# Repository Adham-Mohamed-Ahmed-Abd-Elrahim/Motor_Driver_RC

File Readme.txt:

A PCB Chip for controlling RC car [LPC1768_Arduino Nano_MPU6050_RF L298N (motor driver)]
Software Used For designing: Eagle

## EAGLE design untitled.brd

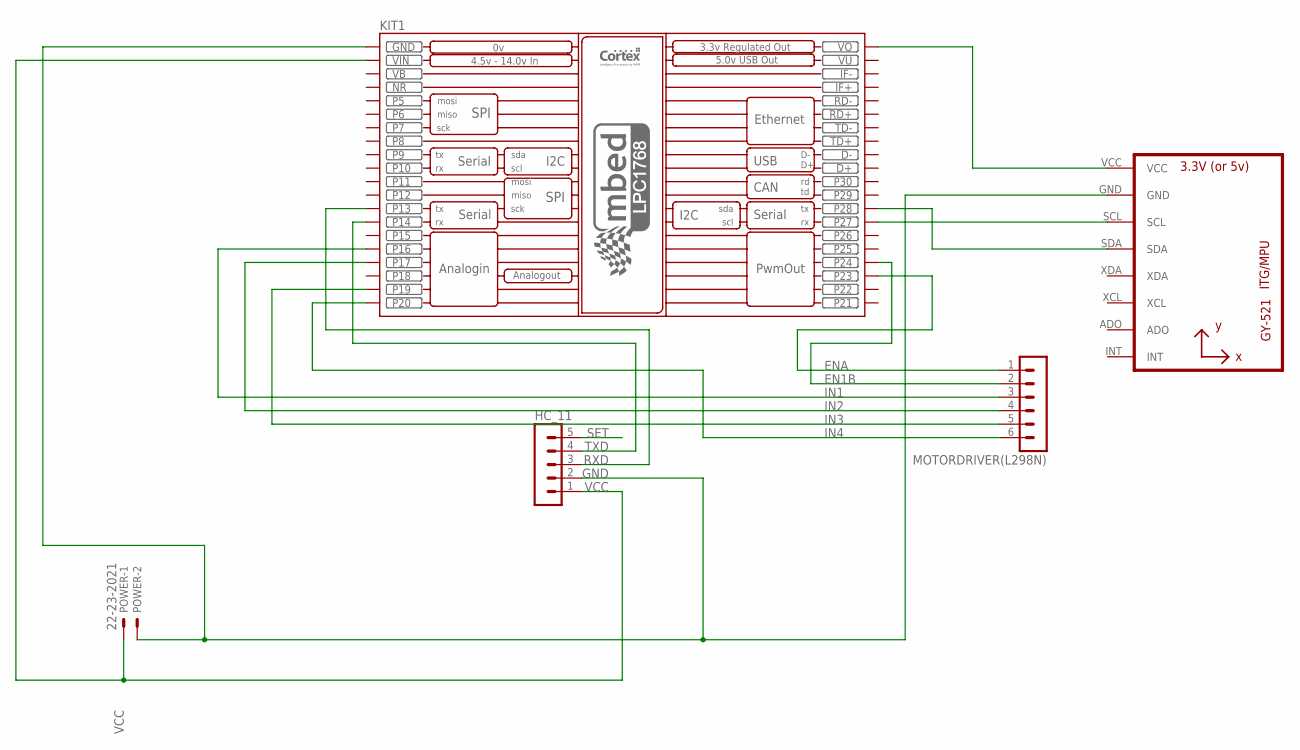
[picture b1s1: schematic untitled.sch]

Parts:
HC_11: MA05-1
KIT1: MBED_NXP_LPC1768; MBED-KIT
MOTORDRIVER(L298N): MA06-1
POWER: 22-23-2021
U1: GY-521MPU6050; GY-521

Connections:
EN1B: KIT1.P$24 (P24), MOTORDRIVER(L298N).2
ENA: KIT1.P$23 (P23), MOTORDRIVER(L298N).1
GND: HC_11.2, KIT1.GND, POWER.2, U1.GND
IN1: KIT1.P$16 (P16), MOTORDRIVER(L298N).3
IN2: KIT1.P$17 (P17), MOTORDRIVER(L298N).4
IN3: KIT1.P$19 (P19), MOTORDRIVER(L298N).5
IN4: KIT1.P$20 (P20), MOTORDRIVER(L298N).6
unnamed: KIT1.VOUT (VO), U1.VCC
NR: KIT1.NR
RXD: HC_11.3, KIT1.P$13 (P13)
SCL: KIT1.P$27 (P27), U1.SCL
SDA: KIT1.P$28 (P28), U1.SDA
SET: HC_11.5
TXD: HC_11.4, KIT1.P$14 (P14)
VB: KIT1.VB
VCC: HC_11.1, KIT1.VIN, POWER.1
VU: KIT1.VU

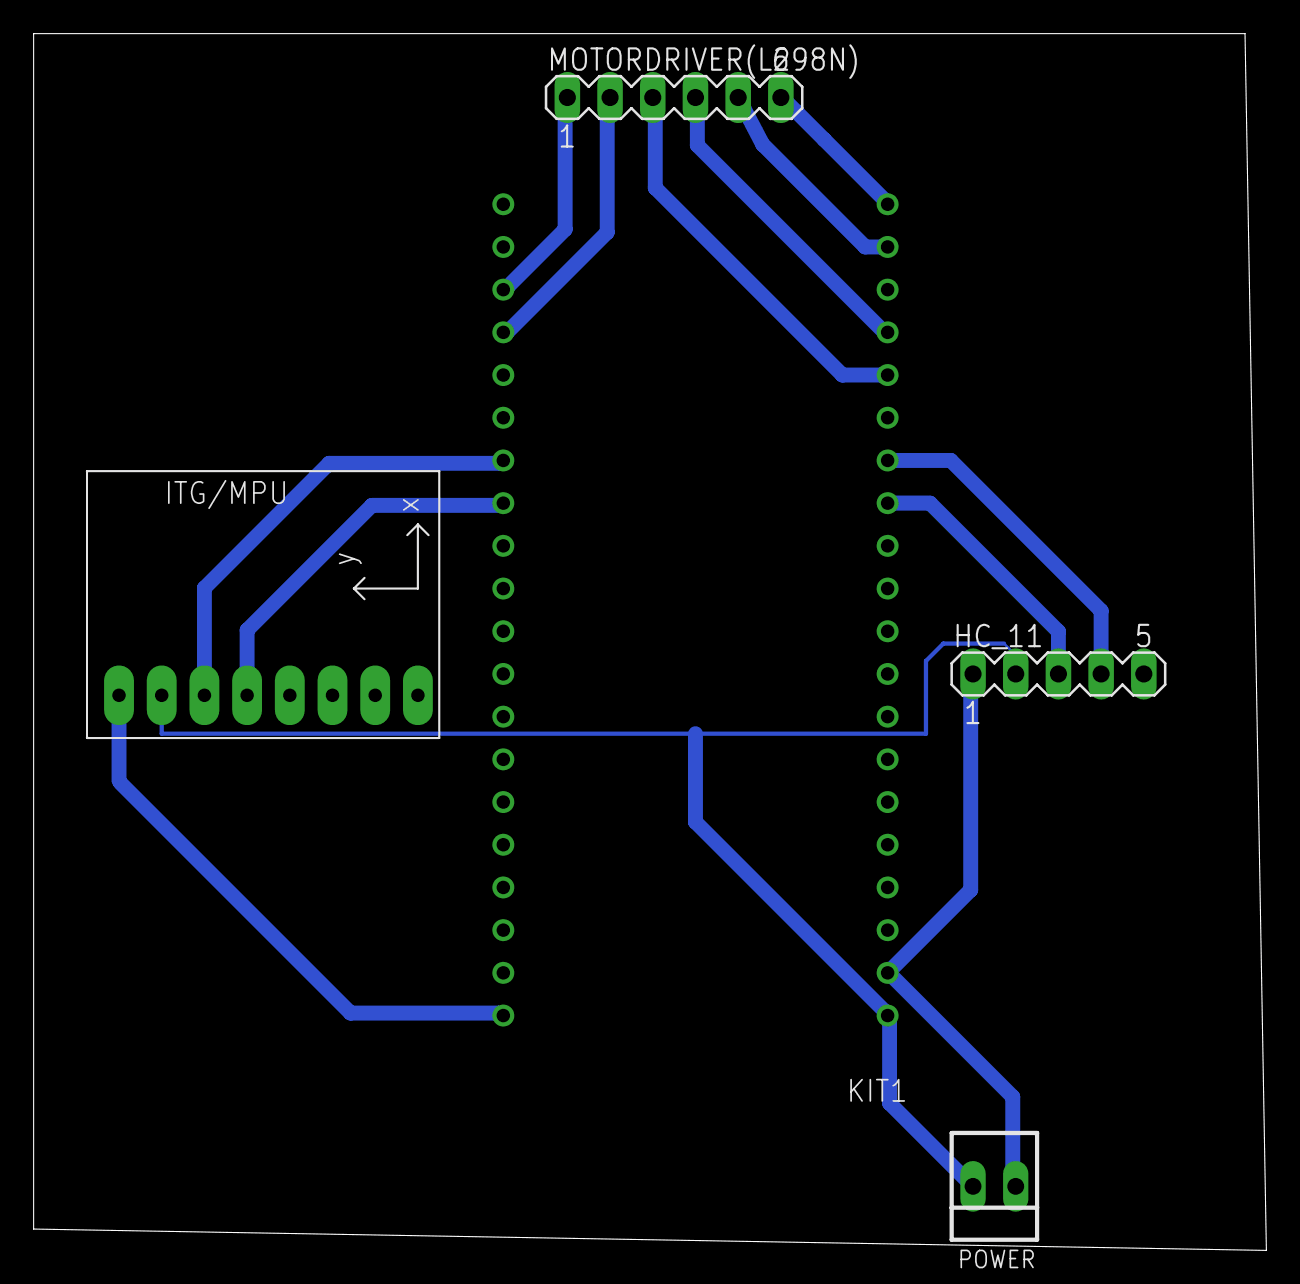
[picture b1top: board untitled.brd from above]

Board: 2 copper layers, 73.3 x 72.4 mm, 5 parts (0 on the bottom side), 13 nets.

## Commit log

2021-08-23 Fianl
2021-09-10 Final Design
